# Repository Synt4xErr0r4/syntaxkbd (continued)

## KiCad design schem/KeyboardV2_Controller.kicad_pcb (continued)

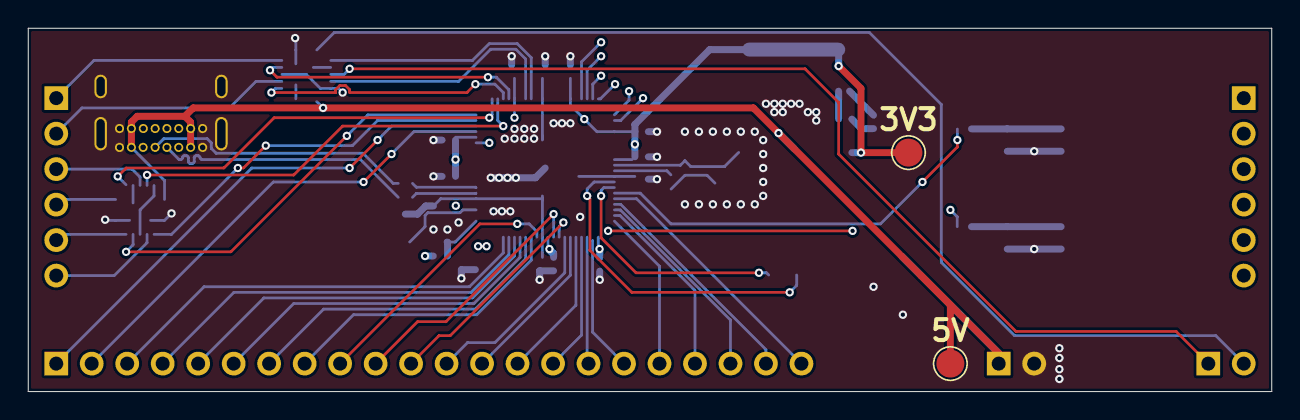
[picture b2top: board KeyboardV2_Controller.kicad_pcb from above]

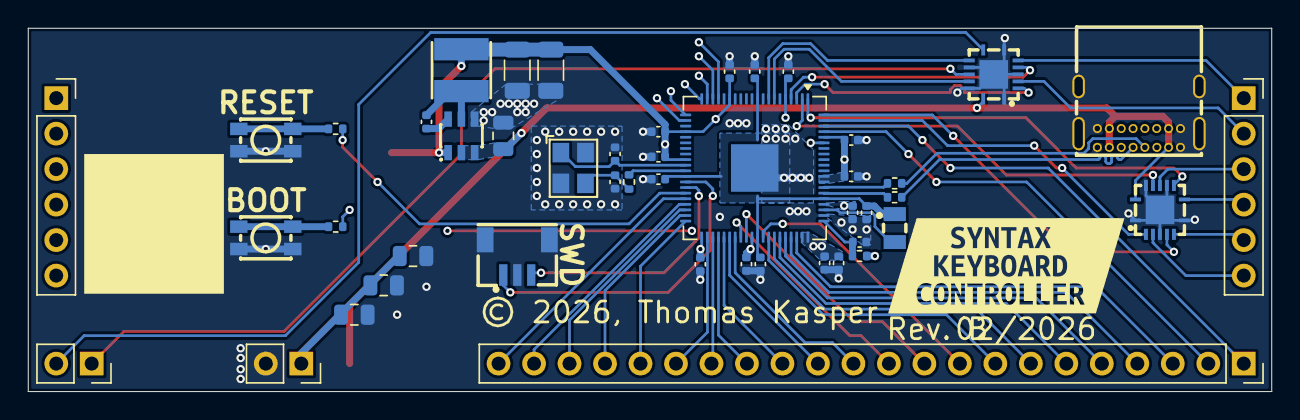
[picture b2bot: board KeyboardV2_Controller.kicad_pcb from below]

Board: 4 copper layers, 89.0 x 26.0 mm, 46 parts (43 on the bottom side), 65 nets.

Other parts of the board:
kibuzzard-699F86BB: G***; kibuzzard-699F86BB
